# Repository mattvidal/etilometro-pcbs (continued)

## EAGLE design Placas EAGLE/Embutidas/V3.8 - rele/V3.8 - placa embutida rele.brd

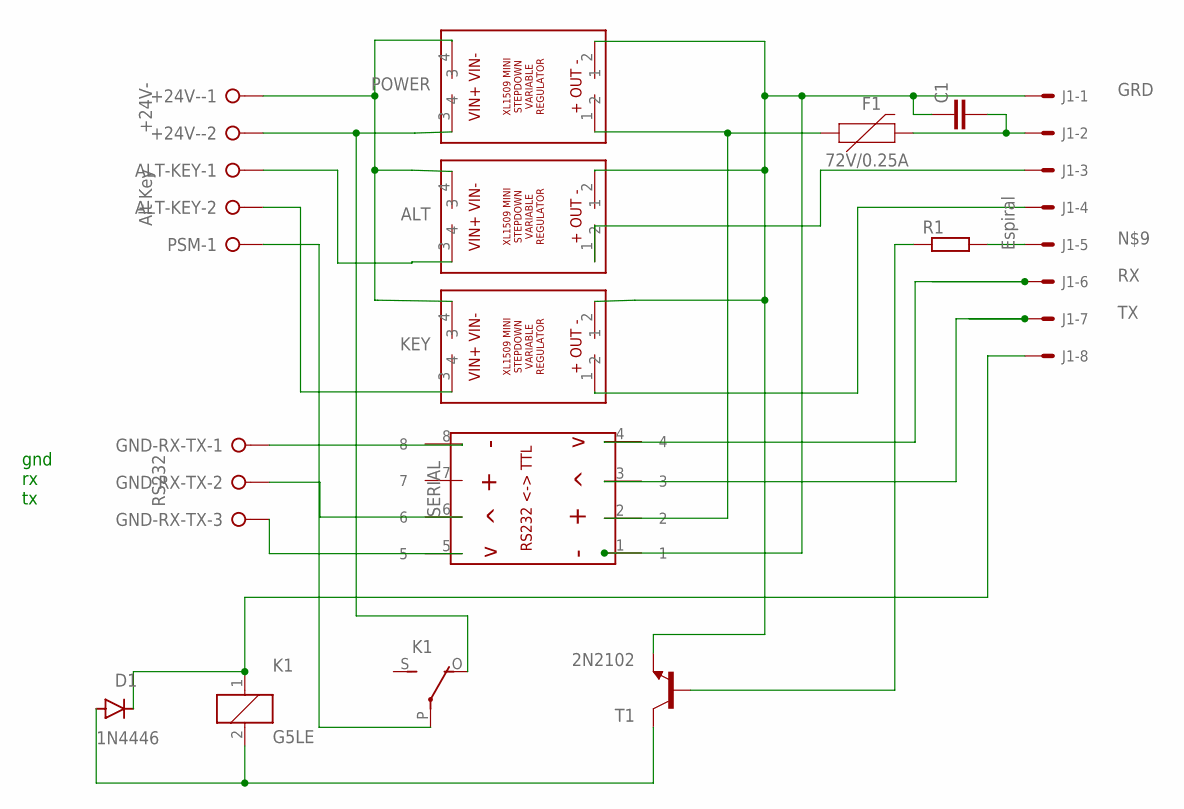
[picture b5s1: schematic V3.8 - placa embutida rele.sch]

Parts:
+24V-: +24V-; W237-132
ALT: XL1509WITH_SMDPADS&THROUGHHOLES; XL1509
ALT-KEY: Alt Key; W237-132
C1: C2,5-3; C2.5-3
D1: 1N4446; DO35-10
F1: 72V/0.25A; PTH
GND-RX-TX: RS232; W237-133
J1: Espiral; 7395-08
K1: G5LE
KEY: XL1509WITH_SMDPADS&THROUGHHOLES; XL1509
POWER: XL1509WITH_SMDPADS&THROUGHHOLES; XL1509
PSM: PSM; W237-132
R1: R-EU_0207/10; 0207/10
SERIAL: MAX3232WITH_SMDPADS&THROUGHHOLES; MAX3232
T1: 2N2102; TO5

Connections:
CHAVE: ALT.1, J1.3
GRD: ALT.2, C1.1, J1.1, KEY.2, POWER.2, SERIAL.1, T1.1 (E)
unnamed: +24V-.1, ALT.4, KEY.4, POWER.4
unnamed: +24V-.2, K1.O, POWER.3
unnamed: F1.P$1 (1), POWER.1, SERIAL.2
unnamed: GND-RX-TX.1, SERIAL.8
unnamed: ALT.3, ALT-KEY.1
unnamed: ALT-KEY.2, KEY.3
unnamed: GND-RX-TX.2, SERIAL.6
unnamed: GND-RX-TX.3, SERIAL.5
unnamed: J1.5, R1.2
unnamed: R1.1, T1.2 (B)
unnamed: C1.2, F1.P$2 (2), J1.2
unnamed: J1.4, KEY.1
unnamed: D1.A, K1.2, T1.3 (C)
unnamed: D1.C, J1.8, K1.1
unnamed: K1.P, PSM.1
RX: J1.6, SERIAL.4
TX: J1.7, SERIAL.3

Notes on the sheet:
gnd rx tx

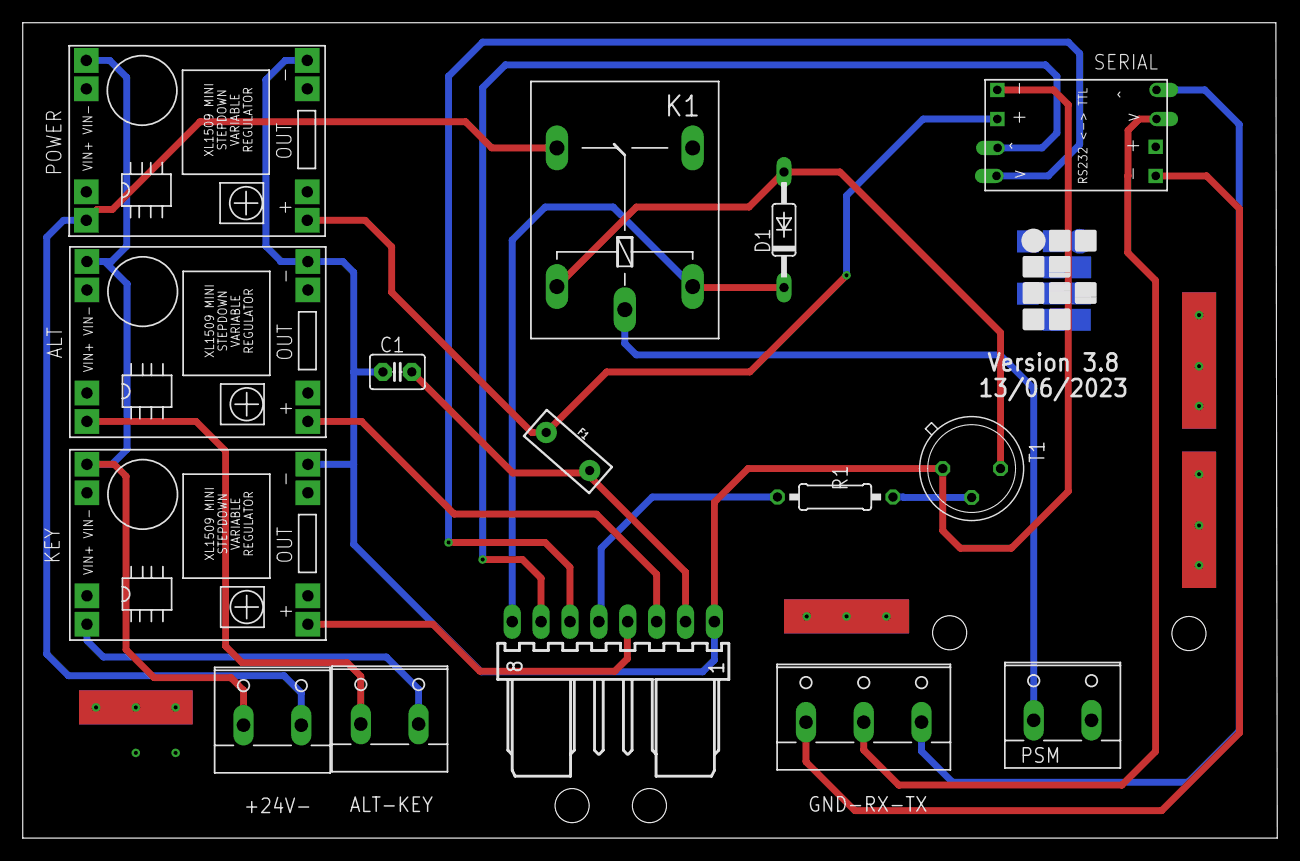
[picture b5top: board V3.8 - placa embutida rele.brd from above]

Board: 2 copper layers, 110.2 x 71.6 mm, 15 parts (0 on the bottom side), 19 nets.

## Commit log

2025-08-19 mod output
2025-08-19 pick and place add
2025-08-20 alterado pn rs232
